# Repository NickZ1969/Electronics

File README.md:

# Electronics
My electronic projects

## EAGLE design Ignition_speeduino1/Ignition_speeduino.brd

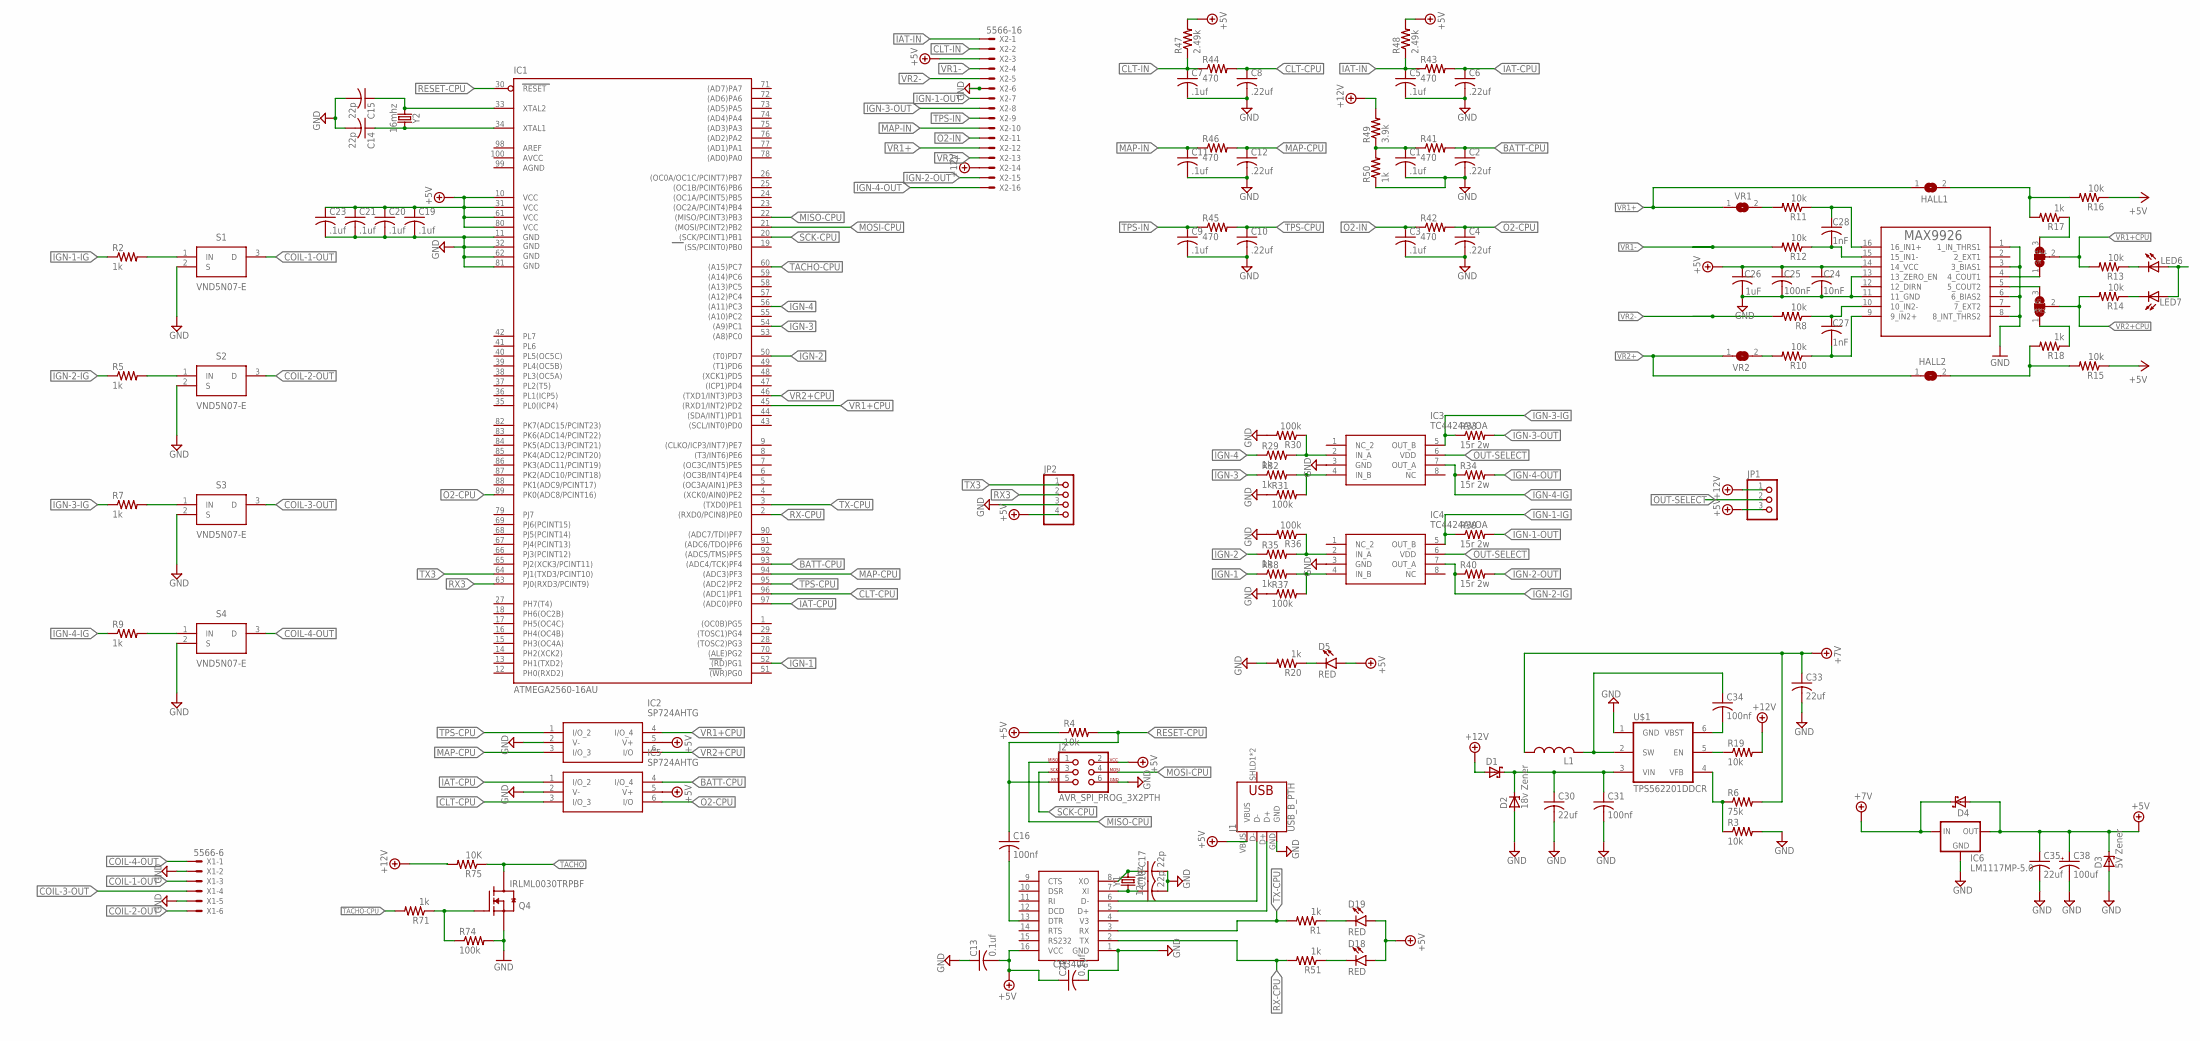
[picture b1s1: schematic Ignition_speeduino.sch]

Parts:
C1, C3, C5, C7, C9, C11, C19, C20, C21, C23: .1uf; C1206
C2, C4, C6, C8, C10, C12: .22uf; C1206
C13, C22: 0.1uf; C1206
C14, C15, C17, C18: 22p; C1206
C16, C31, C34: 100nf; C1206
C24: 10nF; C1206
C25: 100nF; C1206
C26: 1uF; C1206
C27, C28: 1nF; C1206
C30, C33, C35: 22uf; C1206
C38: 100uf; 153CLV-0605
D1, D4: SCHOTTKY-DIODESMD; SMB
D2: 18v Zener; SMB
D3: 5V Zener; SMB
D5, D18, D19: RED; LED-1206
HALL1: HALL1; SJ
HALL2: HALL2; SJ
IC1: ATMEGA2560-16AU; TQFP100
IC2, IC5: SP724AHTG; SOT95P280X145-6N
IC3, IC4: TC4424AVOA; SOIC127P600X175-8N
IC6: LM1117MP-5.0; SOT223
J1: USB_B_PTH; USB-B-PTH
J2: AVR_SPI_PROG_3X2PTH; 2X3
JP1: PINHD-1X3; 1X03
JP2: PINHD-1X4; 1X04
L1: L-USPIS2816; PIS2816
LED6, LED7: LEDCHIP-LED0805; CHIP-LED0805
Q4: IRLML0030TRPBF; SOT95P280X135-3N
R1, R2, R5, R7, R9, R17, R18, R20, R29, R32, R35, R38, R50, R51, R71: 1k; R1206
R3, R4, R8, R10, R11, R12, R13, R14, R15, R16, R19: 10k; R1206
R6: 75k; R1206
R30, R31, R36, R37, R74: 100k; R1206
R33, R34, R39, R40: 15r 2w; R2512
R41, R42, R43, R44, R45, R46: 470; R1206
R47, R48: 2.49k; R1206
R49: 3.9k; R1206
R75: 10K; R1206
S1, S2, S3, S4: VND5N07-E; TO-252-(DPAK)_1
U$1: TPS562201DDCR; SOT23-6L
U$2: CH340G; SOIC16
U$10: MAX9926; QSOP16
VR1, VR2: SJ2W; SJ_2
VR1+: VR1; SJ
VR2+: VR2; SJ
X1: 5566-6
X2: 5566-16
Y1: 12mhz; HC49U
Y2: 16mhz; HC49U

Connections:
+5V: C13.2, C19.1, C20.1, C21.1, C22.1, C23.1, C24.1, C25.1, C26.1, C35.1, C38.+, D3.C, D4.A, D5.A, D18.A, D19.A, IC1.10 (VCC), IC1.31 (VCC1), IC1.61 (VCC2), IC1.80 (VCC3), IC2.5 (V+), IC5.5 (V+), IC6.2 (OUT), IC6.4 (OUT), J1.VBUS, J2.2, JP1.3, JP2.4, LED6.A, LED7.A, R4.1, R15.1, R16.1, R47.2, R48.2, U$2.16 (VCC), U$10.14 (14_VCC), X2.3
+7V: C33.1, D4.C, IC6.3 (IN), L1.1, R6.2
+12V: D1.A, JP1.1, R19.2, R49.2, R75.2, X2.14
AGND: IC1.99 (AGND)
AVCC: IC1.100 (AVCC)
BATT-CPU: C2.1, IC1.93 ((ADC4/TCK)PF4), IC5.4 (I/O_4), R41.2
CLT-CPU: C8.1, IC1.96 ((ADC1)PF1), IC5.3 (I/O_3), R44.2
CLT-IN: C7.1, R44.1, R47.1, X2.2
COIL-1-OUT: S1.3 (D), X1.3
COIL-2-OUT: S2.3 (D), X1.6
COIL-3-OUT: S3.3 (D), X1.4
COIL-4-OUT: S4.3 (D), X1.1
GND: C1.2, C2.2, C3.2, C4.2, C5.2, C6.2, C7.2, C8.2, C9.2, C10.2, C11.2, C12.2, C13.1, C14.2, C15.2, C17.2, C18.2, C19.2, C20.2, C21.2, C22.2, C23.2, C24.2, C25.2, C26.2, C30.2, C31.2, C33.2, C35.2, C38.-, D2.A, D3.A, IC1.11 (GND), IC1.32 (GND1), IC1.62 (GND2), IC1.81 (GND3), IC2.2 (V-), IC3.3 (GND), IC4.3 (GND), IC5.2 (V-), IC6.1 (GND), J1.GND, J2.6, JP2.3, Q4.2 (S), R3.2, R20.2, R30.2, R31.1, R36.2, R37.1, R50.1, R74.2, S1.2 (S), S2.2 (S), S3.2 (S), S4.2 (S), U$1.1 (GND), U$2.1 (GND), U$10.1 (1_IN_THRS1), U$10.3 (3_BIAS1), U$10.6 (6_BIAS2), U$10.8 (8_INT_THRS2), U$10.11 (11_GND), U$10.13 (13_ZERO_EN), X1.2, X1.5, X2.6
IAT-CPU: C6.1, IC1.97 ((ADC0)PF0), IC5.1 (I/O_2), R43.2
IAT-IN: C5.1, R43.1, R48.1, X2.1
IGN-1: IC1.52 ((RD)PG1), R38.1
IGN-1-IG: IC4.5 (OUT_B), R2.1, R39.1
IGN-1-OUT: R39.2, X2.7
IGN-2: IC1.50 ((T0)PD7), R35.1
IGN-2-IG: IC4.7 (OUT_A), R5.1, R40.1
IGN-2-OUT: R40.2, X2.15
IGN-3: IC1.54 ((A9)PC1), R32.1
IGN-3-IG: IC3.5 (OUT_B), R7.1, R33.1
IGN-3-OUT: R33.2, X2.8
IGN-4: IC1.56 ((A11)PC3), R29.1
IGN-4-IG: IC3.7 (OUT_A), R9.1, R34.1
IGN-4-OUT: R34.2, X2.16
MAP-CPU: C12.1, IC1.94 ((ADC3)PF3), IC2.3 (I/O_3), R46.2
MAP-IN: C11.1, R46.1, X2.10
MISO-CPU: IC1.22 ((MISO/PCINT3)PB3), J2.1
MOSI-CPU: IC1.21 ((MOSI/PCINT2)PB2), J2.4
unnamed: R2.2, S1.1 (IN)
unnamed: J1.D+, U$2.5 (D+)
unnamed: J1.D-, U$2.6 (D-)
unnamed: R5.2, S2.1 (IN)
unnamed: C14.1, IC1.34 (XTAL1), Y2.2
unnamed: C15.1, IC1.33 (XTAL2), Y2.1
unnamed: R7.2, S3.1 (IN)
unnamed: D5.C, R20.1
unnamed: C16.2, U$2.13 (DTR)
unnamed: R9.2, S4.1 (IN)
unnamed: HALL1.2, R16.2, R17.2
unnamed: C27.1, R8.1, U$10.10 (10_IN2-)
unnamed: C28.2, R12.1, U$10.15 (15_IN1-)
unnamed: C18.1, U$2.7 (XI), Y1.1
unnamed: C17.1, U$2.8 (XO), Y1.2
unnamed: R10.2, VR2+.2
unnamed: U$10.4 (4_COUT1), VR1.1
unnamed: R17.1, VR1.3
unnamed: U$10.5 (5_COUT2), VR2.3
unnamed: R18.1, VR2.1
unnamed: C30.1, C31.1, D1.C, D2.C, U$1.3 (VIN)
unnamed: C34.2, U$1.6 (VBST)
unnamed: R19.1, U$1.5 (EN)
unnamed: HALL2.2, R15.2, R18.2
unnamed: Q4.1 (G), R71.1, R74.1
unnamed: IC3.2 (IN_A), R29.2, R30.1
unnamed: IC3.4 (IN_B), R31.2, R32.2
unnamed: C27.2, R10.1, U$10.9 (9_IN2+)
unnamed: C28.1, R11.1, U$10.16 (16_IN1+)
unnamed: IC4.2 (IN_A), R35.2, R36.1
unnamed: IC4.4 (IN_B), R37.2, R38.2
unnamed: C1.1, R41.1, R49.1, R50.2
unnamed: R11.2, VR1+.2
unnamed: LED7.C, R14.1
unnamed: LED6.C, R13.1
unnamed: D19.C, R1.1
unnamed: D18.C, R51.1
O2-CPU: C4.1, IC1.89 (PK0(ADC8/PCINT16)), IC5.6 (I/O), R42.2
O2-IN: C3.1, R42.1, X2.11
OUT-SELECT: IC3.6 (VDD), IC4.6 (VDD), JP1.2
RESET-CPU: C16.1, IC1.30 (RESET), J2.5, R4.2
RX3: IC1.63 (PJ0(RXD3/PCINT9)), JP2.2
RX-CPU: IC1.2 ((RXD0/PCIN8)PE0), R51.2, U$2.2 (TX)
SCK-CPU: IC1.20 ((SCK/PCINT1)PB1), J2.3
SW: C34.1, L1.2, U$1.2 (SW)
TACHO: Q4.3 (D), R75.1
TACHO-CPU: IC1.60 ((A15)PC7), R71.2
TPS-CPU: C10.1, IC1.95 ((ADC2)PF2), IC2.1 (I/O_2), R45.2
TPS-IN: C9.1, R45.1, X2.9
TX3: IC1.64 (PJ1(TXD3/PCINT10)), JP2.1
TX-CPU: IC1.3 ((TXD0)PE1), R1.2, U$2.3 (RX)
VFB: R3.1, R6.1, U$1.4 (VFB)
VR1+: HALL1.1, VR1+.1, X2.12
VR1+CPU: IC1.45 ((RXD1/INT2)PD2), IC2.4 (I/O_4), R13.2, VR1.2
VR1-: R12.2, X2.4
VR2+: HALL2.1, VR2+.1, X2.13
VR2+CPU: IC1.46 ((TXD1/INT3)PD3), IC2.6 (I/O), R14.2, VR2.2
VR2-: R8.2, X2.5

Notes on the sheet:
HALL

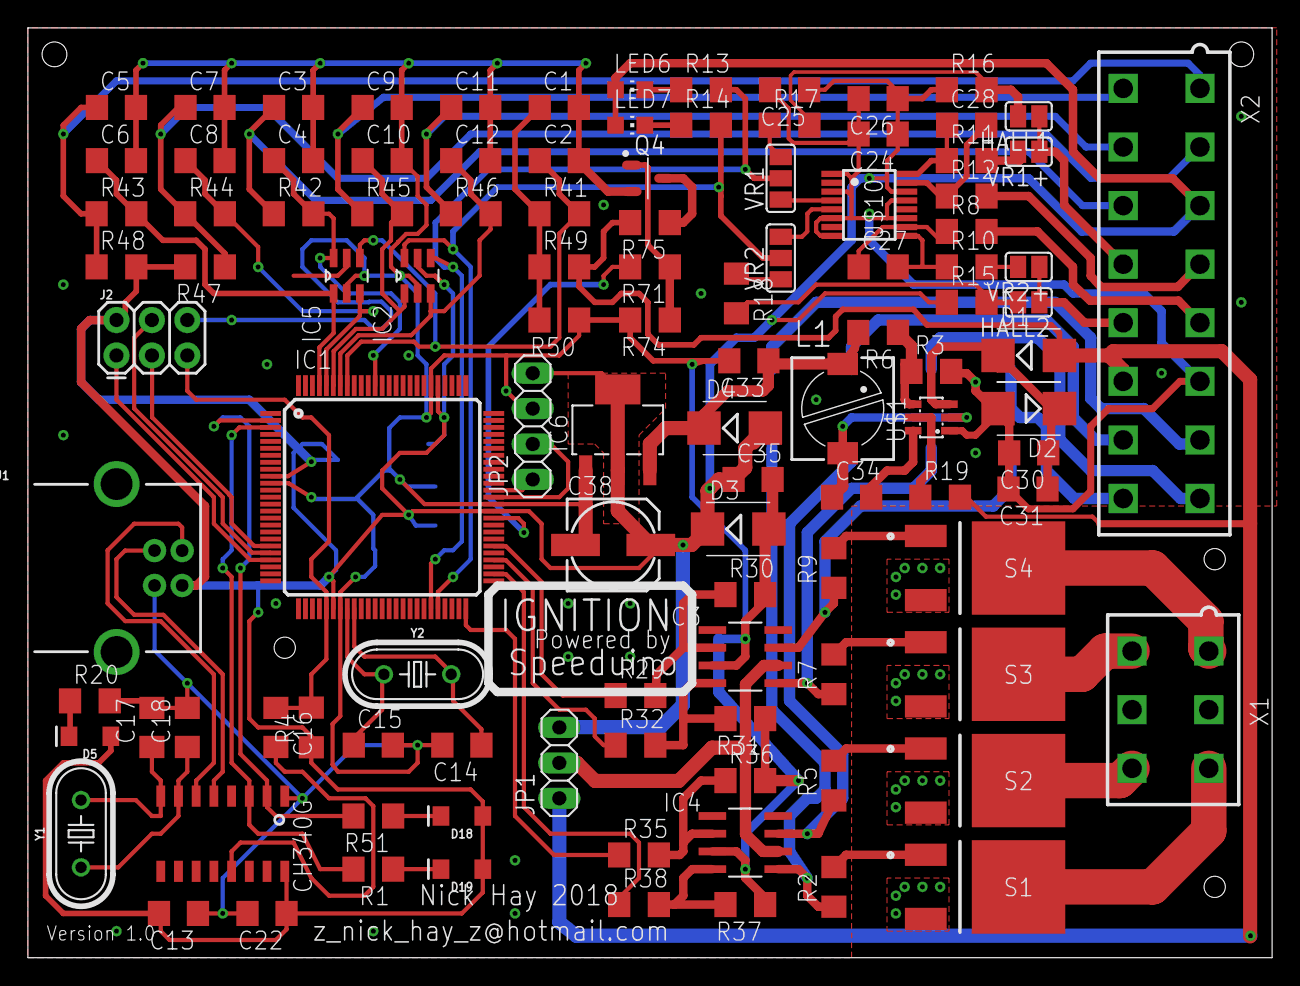
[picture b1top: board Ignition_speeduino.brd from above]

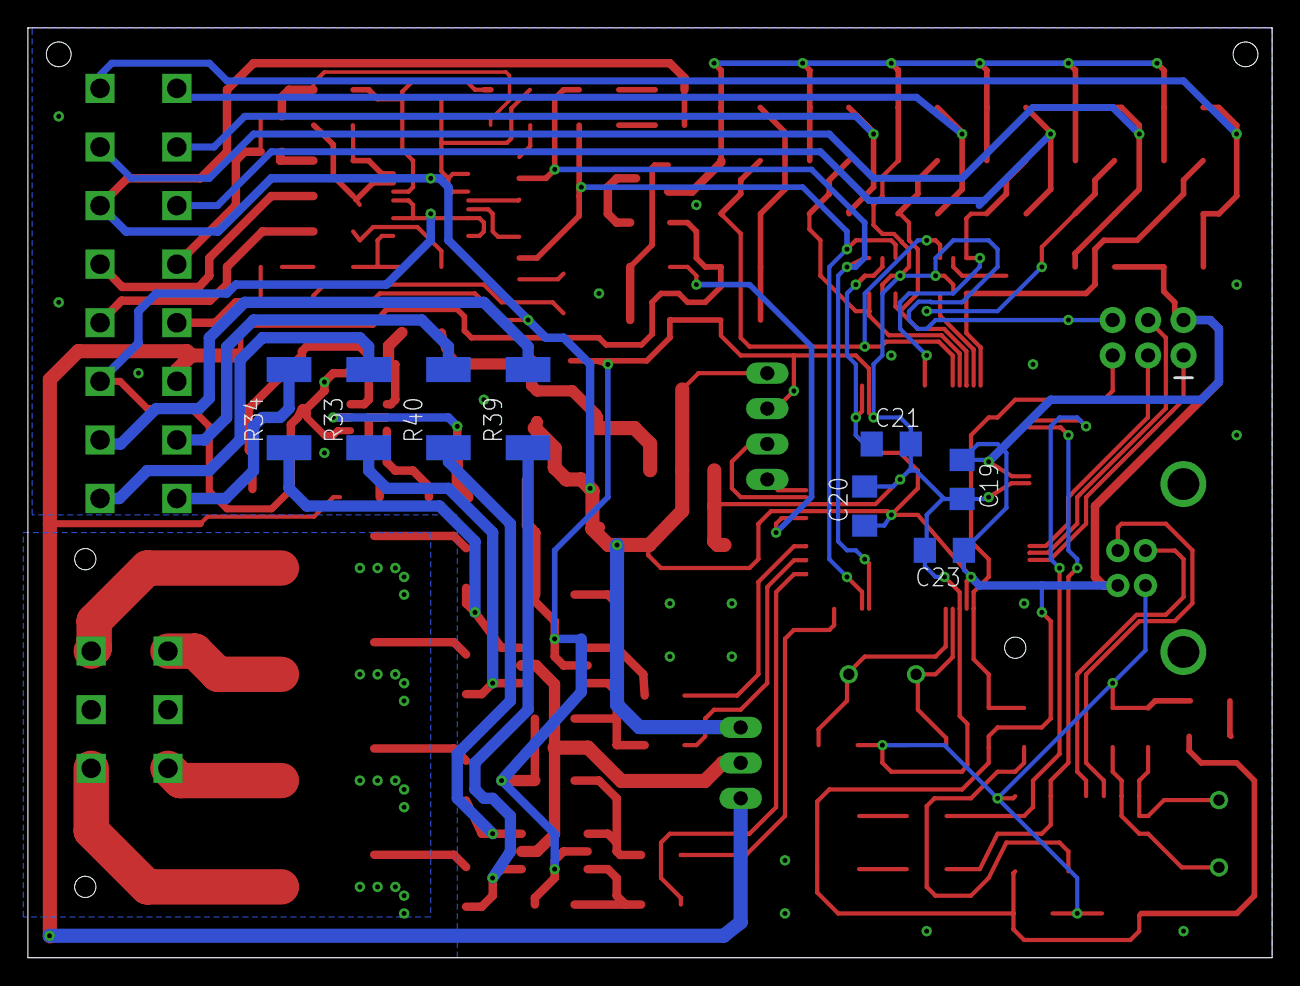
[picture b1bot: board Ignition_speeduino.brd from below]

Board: 2 copper layers, 89.2 x 66.7 mm, 118 parts (8 on the bottom side), 87 nets.

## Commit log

2019-01-24 Licence.txt
2019-01-31 Add files via upload
    schematic of Teensy 3.5 8x8
2019-02-11 Add files via upload
    utils.ino for use with teensy 8x8 for pin definition, use speeduino version 0.4 for board type.
2019-02-12 Delete utils.ino
    Pin def has been moved to int
2019-02-12 Add files via upload
    Pin Definitions for Teensy 8x8 Use speeduino v0.4 in board selection TunerStudio
2019-02-14 Add files via upload
    Needed for firmware December and back. Pin definitions, use V0.4 board type.
2019-03-07 Add files via upload
    Feb 2019 March 7 update
2019-04-02 Fixed conflicting pins
2019-04-02 Add files via upload
    Fix conflicting pins
2019-04-14 Add fixed BARO pin A21 For Superseal Version
2019-04-14 Added "Teensy 8x8" in Board list for TunerStudio
2019-04-15 Added "Teensy 8x8" for pin definitions
2019-04-15 Baro Pin A21 for Teensy 8x8 V2
2019-04-15 Added Pin Definition for teensy 8x8

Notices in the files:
parts and their libraries:
SparkFun-LED: Licensing: Creative Commons ShareAlike 4.0 International - https://creativecommons.org/licenses/by-sa/4.0
